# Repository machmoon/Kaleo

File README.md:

# Hardy

**End-to-end PCB design. Describe a board in plain language, get a placed KiCad
layout back — with the reasoning shown and every claim cited.**

**Two names, one thing.** *Hardy* is who you talk to — the AI hardware engineer and
the desktop app in [`app/`](app/). (The spoken wake word is still "Ada", from the
app's previous name.) *Silkscreen* is the engine underneath: the Python package, the
`silkscreen` command, and this repository. Hardy is a client of Silkscreen; either
can be used without the other.

Silkscreen reads the datasheets, proposes a circuit, refuses to build it if it does
not validate, **draws a schematic**, generates the footprints, places the board with a
CP-SAT solver, **routes the copper**, and then argues against its own design and tells
you what it thinks is wrong.

**Silkscreen is a Python program you run.** The command line is the product; the web UI
is a viewer for what it produced, and is the less-supported path — see
[Which interface](#which-interface).

<!-- SCREENSHOTS WANTED — do not uncomment until the files exist under docs/img/:
     docs/img/review.png    the review pane with findings and citations
     docs/img/schematic.png the Schematic tab
-->

---

## Quickstart

Python 3.11 or newer. **No KiCad install or API key is needed to install it or
run the whole test suite. After dependencies are installed, the suite itself
makes no network calls.**

**One command.** It finds a Python 3.11+, creates `.venv`, installs the engine editable
with its extras, and builds the web UI if Node 22+ is on your PATH (skipped, not fatal,
if it isn't). Nothing is written outside the repo and it never uses `sudo`:

```bash
git clone https://github.com/machmoon/silkscreen && cd silkscreen
./scripts/install.sh                                           # macOS / Linux
powershell -ExecutionPolicy Bypass -File scripts\install.ps1   # Windows
```

Then, optionally, one command to configure a key and one to open the app:

```bash
./.venv/bin/silkscreen setup    # writes .env; never echoes the key back
./.venv/bin/silkscreen serve    # starts the API + UI and opens the Hardy desktop app (--web for the browser)
```

<details>
<summary><b>Or install by hand</b> (three lines, same result)</summary>

```bash
python3 -m venv .venv
./.venv/bin/pip install -e ".[dev,agents,cloud,adk,cad]"   # Windows: .venv\Scripts\pip
./.venv/bin/python -m pytest -q                    # offline; no keys required
```
</details>

<details>
<summary><b>Or run the web UI in Docker</b> (no Python or Node on your machine)</summary>

```bash
docker build -t silkscreen .
docker run -p 8080:8080 -e GOOGLE_API_KEY=... silkscreen   # http://localhost:8080
```

The image builds the Svelte bundle in a Node stage and serves it from the Python
service, same origin as the API.
</details>

Then place a board — no API key, nothing to configure, and it finishes in about
20 seconds:

```bash
./.venv/bin/python scripts/demo.py
```

To go from a prompt to a board you need a Gemini key (`GOOGLE_API_KEY`); everything
else works without one:

```bash
./.venv/bin/silkscreen setup    # or: cp .env.example .env, and edit it
./.venv/bin/silkscreen "a 3.3V motor driver around an STM32F103" -o board.kicad_pcb
```

`setup` and `serve` are the only subcommands; any other argument is the plain-language
intent, so `silkscreen "..."` and `python -m silkscreen "..."` are the same generator.

One run leaves you a KiCad project, one file per stage:

```
wrote board.kicad_pro          ← open this in KiCad
wrote board.kicad_sch          ← the schematic
wrote board.placed.kicad_pcb   ← after placement, before any copper
wrote board.kicad_pcb          ← routed
```

Every stage is a real KiCad file you can open and inspect on its own, so you can see
where a design went wrong instead of only seeing the last artifact.

```
3356 tests collected — no network, no API key, no KiCad install
```

**Next:** [full install guide and troubleshooting](docs/install.md) ·
[contributing](CONTRIBUTING.md) · [how it works](#prompt-to-pcb)

**Download:** [tagged releases](https://github.com/machmoon/silkscreen/releases) carry the
Python wheel and built web UI. The native **Hardy** macOS shell currently runs
from a checkout; `.dmg` packaging, signing, and notarization are not yet built.

---

## Which interface

| | `python -m silkscreen` *(recommended)* | Web UI |
|---|---|---|
| Schematic (`.kicad_sch`) | ✅ | ❌ not surfaced |
| Routed copper | ✅ | ✅ in the downloaded file only — the board well draws placement, not tracks |
| Per-stage files you can open | ✅ | ❌ final board only |
| KiCad project (`.kicad_pro`) | ✅ | ❌ |
| Adversarial review, findings, citations | ✅ text | ✅ nicer to read |

**The CLI is still the complete project-output path.** The web UI (`service/` +
`frontend/`) now starts with a persistent orchestrator chat, shows the observable model,
tool, validation, and retry activity, and hands you compact cards for the schematic,
placement diagram, review, and final `.kicad_pcb`. It still does not return the native
`.kicad_sch`/`.kicad_pro` or draw routed tracks, so use the CLI when those files matter.

---

## How you are meant to run this

**Not to run Silkscreen. Yes, strongly recommended, to do anything with what it makes.**

Silkscreen writes the KiCad formats itself, so nothing in the pipeline shells out to
KiCad, imports `pcbnew`, or touches your mouse. But the output *is* a KiCad project,
and without KiCad you have files you cannot open, check, or fabricate. Silkscreen's
router leaves hard nets unrouted on purpose and tells you which — finishing them is
work you do in KiCad. Install it unless you have a specific reason not to.

| | Without KiCad | With KiCad *(strongly recommended)* |
|---|---|---|
| Generate a schematic and a routed board from a prompt | ✅ | ✅ |
| Run the test suite | ✅ | ✅ |
| Deploy the service, use the MCP server or the Slack bot | ✅ | ✅ |
| **See the schematic and the board** | ❌ | ✅ |
| **Finish the nets the router left unrouted** | ❌ | ✅ |
| **Run DRC and electrical rules check** | ❌ | ✅ |
| **Export Gerbers and get it fabricated** | ❌ | ✅ |

Skip KiCad if you are running Silkscreen in CI, on a server, or inside another tool
that consumes the file. Install it if you are a person who wants to see a board.
Platform-by-platform commands are in [docs/install.md](docs/install.md#kicad-optional-but-recommended).

---

## Status

| Component | State |
|---|---|
| `kicad.py` — `.kicad_pcb` read/write | **Working** · 33 tests |
| `packing.py` — CP-SAT placer | **Working** · 44 tests |
| `netlist.py` — validated circuit IR | **Working** · 31 tests |
| `schematic.py` — `.kicad_sch` + `.kicad_pro` emission | **Working** · 38 tests · KiCad ERC clean |
| `routing.py` — two-layer grid autorouter | **Working, partial by design** · 54 tests — see below |
| `footprints.py` + `board.py` — land patterns, board emission | **Working** · 35 tests |
| `agents/` — datasheet, propose, review, pipeline | **Working** · 72 tests |
| `agents/adk/` — ADK dynamic-workflow driver for the pipeline | **Working** · 21 tests |
| `agents/retrieval.py` — page-cited datasheet retrieval | **Working** · 15 tests |
| `agents/resilience.py` — provider failover | **Working** · 31 tests |
| `fab.py` — Gerber, Excellon, BOM, pick-and-place | **Working** · fab package export |
| `order.py` — order options, manufacturability preflight | **Working** · blocks an unrouted board |
| `sourcing.py` + `models3d.py` — BOM with distributor-checked MPNs, probed datasheets, library 3D models | **Working** · an MPN is `verified` only when Mouser lists that exact part number (`MOUSER_API_KEY` required); otherwise `proposed`, with `verify_error` saying why. `verified` means listed, **not** in stock and **not** the right package |
| `mcp/` — MCP server over stdio | **Working** · 43 tests |
| `audit/` — optional visual design review | **Working** · 52 tests |
| `service/` — Cloud Run + Firestore cache | **Working** · 158 tests · deployed once to <https://silkscreen-vqdj4x5qbq-uc.a.run.app>, **currently down** (`/readyz` → 500, `/` → 503 on 2026-09-06, unhealthy since 2026-09-05). Redeploy with `scripts/deploy.sh` and re-verify with `curl -s -o /dev/null -w '%{http_code}' <url>/readyz` before a demo |
| `slackbot/` — Slack bot over the pipeline | **Working** · untested against a live workspace |
| `googleapps/` — Chat, Gmail and Calendar delivery over the pipeline | **Working** · untested against live Google APIs |
| `specreview.py` + the `spec_review` destination — a run's open questions become a booked meeting | **Working** · the Calendar half is untested against live Google APIs |
| `zoombot/` — Zoom front end over RTMS | **Partial by design** · receive and chat halves built, tested offline only; audio out is a spec plus a refusing stub; never run against a live Zoom account |
| `teamsbot/` — Microsoft Teams front end over Graph | **Partial by design** · transcript and chat halves built, tested offline only; the calling bot answers 501; never run against a live tenant |
| `GET /integrations` + the desktop Integrations panel | **Working** · read-only configuration state, never a secret and never a live call |
| `frontend/` — Svelte review UI, served by the service | **Working** · persistent orchestrator chat, expandable traces, session JSON, review, schematic, placement and board tabs; spoken intent and findings read aloud via the browser's own Web Speech API (dictation on the intent and clarification fields in Chrome/Edge — Firefox has no recognition API and gets a notice; findings read by `speechSynthesis` with a stop control; never auto-started). Local-Whisper dictation is not built (`vendor/openwhispr/` is the reference) |
| `engine/silkscreen/placement/` — verifier-grounded repair and company profiles | **Working** · deterministic and Gemini policies; experimental providers are opt-in |
| `constraints.py` — approved build contract and post-route receipt | **Working** · opt-in, fail-closed, and deterministically tested |
| Voice / talk input | **Working** · push-to-talk and "Ada" wake word in the desktop overlay (ear toggle, off by default, paid windows capped at 15); the web SPA's separate browser Web Speech dictation and read-aloud are listed under `frontend/` |
| `app/` — the Hardy desktop overlay (Tauri) | **Working** · approval-gated step strip over a live KiCad, order step with GLB export, in-app 3D board viewer (`ModelViewer`), Workspace delivery panel |
| Guided cursor | **Half built** · the in-webview pointer ships (`frontend/src/lib/guide.js`, `GuidePointer.svelte`, "Show me" on a finding); pointing at anything *outside* our own window — KiCad, a terminal, the OS — is **not built**, and there is no screen capture, accessibility-tree read or OS overlay behind it |
| `spice/` — typed testbenches, decks, measurements, signed-margin assertions | **Working as a library** · reached today only by the MCP tools, `scripts/simulate_demo.py` and direct calls; **no pipeline stage, ADK node, CLI flag or service route builds a deck**, so a generated board is never simulated |

Every module above is covered by tests that run with no network, no API key, and no
KiCad install. The count is deliberately not quoted here — it drifts, and
`scripts/check_docs.py` fails CI when a quoted one goes stale.

---

## PCB placement agent

After the normal placer produces a board, Silkscreen projects its canonical
integer-nanometre geometry into a bounded millimetre verifier, accepts only
score-improving moves, writes accepted positions back to the canonical board,
and only then routes copper. If the company profile needs more edge or clearance
space than CP-SAT's tight outline provides, the adapter minimally expands that
outline before repair. The placement view shows the before and after geometry
together with a receipt for every proposed move.

The legality boundary is deterministic: board bounds, courtyard clearance,
keepouts, and fixed parts. Company preferences are lower-priority terms for
functional grouping, connector access, compactness, and thermal separation.
Gemini may propose `PLACE` and `MOVE` actions, but it cannot override the
verifier. The model-free policy remains available for reproducible runs.

Ollama, Tinker, hybrid policy selection, and training traces are behind an
**Experimental placement features** control that is off by default and enforced
again by the service. Trace recording requires separate explicit consent.
The focused lab keeps corrections in that browser tab's session storage. The
public endpoint applies feedback to one request only; durable shared company
memory remains intentionally unavailable until tenant authentication exists.

The focused `/?mode=placement` lab remains available for comparing the two
included company profiles. See [the placement-agent architecture](docs/placement-agent.md)
for the agent, supervised fine-tuning, reinforcement learning, and verifier boundary.

---

## Approved build constraints

The main prompt form has an optional **Verified constraints** editor. It is collapsed
and disabled by default, so the ordinary prompt-only demo is unchanged. When enabled,
the editor requires exact net names, measurable limits, and an explicit engineer
approval. Any prompt or manifest edit clears that approval. Version 2 manifests are
strict: unknown fields, unknown constraint kinds, duplicate ownership, unsupported
layers, and zero-area physical limits are rejected before cache access or a model call.

The approved manifest is included in the circuit-proposal context, then checked again
against the validated circuit, final placement, and routed copper. The receipt reports
verified, violated, unresolved, and not-required checks for connectivity, routed
geometry, pull-ups, board outline, keepouts, fixed placements, and other declared
limits. Claims that need evidence this engine does not have—such as controlled
impedance without a stackup/field solver, plane continuity, component height, or a
complete voltage-drop model—remain **unresolved** and block production-promotion
eligibility rather than being guessed.

This is currently a post-build eligibility receipt, not a second placer or router.
Board dimensions, keepouts, fixed locations, and soft weights do not yet configure the
CP-SAT or A* solve directly. Soft terms score the one generated result for comparison;
they do not prove that alternatives were ranked. A blocked receipt leaves the generated
KiCad artifact available for inspection, but the orchestrator identifies it as not
eligible for production promotion.

---

## Prompt to PCB

```bash
echo 'GOOGLE_API_KEY=...' >> .env
python -m silkscreen "a 3.3V motor driver board around an STM32F030" \
    --datasheet "AMS1117-3.3=https://.../ams1117.pdf" \
    -o board.kicad_pcb
```

```
intent ─► datasheets ─► propose/validate ─► CP-SAT place ─► verifier repair
                                                                │
               .kicad_pcb ◄─ route ◄─ .kicad_sch + placed board ◄┘
                     │
                     └─► adversarial review
```

| Stage | Module | Artifact |
|---|---|---|
| Datasheet reading (Gemini native PDF vision) | `agents/datasheet.py` | |
| Retrieval over datasheet text, page-cited | `agents/retrieval.py` | |
| Circuit proposal into the IR | `agents/propose.py` | |
| Validation + bounded repair loop | `netlist.py` | |
| Schematic drawing | `schematic.py` | `.kicad_sch`, `.kicad_pro` |
| Footprint generation, board emission | `footprints.py`, `board.py` | |
| Placement | `packing.py` | `.placed.kicad_pcb` |
| Verifier-gated placement repair | `placement/` | placement receipt |
| Copper routing | `routing.py` | `.kicad_pcb` |
| Part sourcing, in the background from placement on | `sourcing.py`, `agents/sourcing.py` | `bom.csv` |
| Approved constraint verification | `constraints.py` | promotion receipt |
| Adversarial review | `agents/review.py` | |

Useful flags: `--no-route` stops after placement, `--no-review` skips the adversarial
pass, `--board-only` writes just the routed `.kicad_pcb`, `--time-limit` sets the
solver budget, `--repairs` how many times a bad proposal goes back to the model,
`--bom` also sources the parts (see [Sourcing the parts](#sourcing-the-parts)), and
`--case` also designs a 3D-printable enclosure — with `--case-style` for a
natural-language case intent ("rounded corners, USB cutout left") and `--rigorous` to run
the case proposal's full strict verify-and-repair loop instead of the demo-fast default,
where a fit failure rides the receipt as a warning rather than blocking the run.

The schematic and the board are drawn by two emitters from one `CircuitSpec`, and both
take their reference designators from `CircuitSpec.assign_refs()` — so `C1` on the
drawing is `C1` on the board. Numbering them separately would give two files that are
each internally consistent and describe different circuits.

Two gates sit between the model and the board.

**Structural.** The proposal goes through the circuit IR before anything is built.
Every validation error is collected and fed back as one repair prompt; the loop is
bounded and `result.repair_rounds` reports how many corrections it took.

**Semantic.** A reviewer re-reads the datasheets and is prompted to *refute* the
design — an agent asked "is this correct?" says yes. Findings are graded
blocker / marginal / note and cite the datasheet page. A part reference the circuit
does not contain is stripped out of the finding that named it; the finding itself
is still shown.

Everything below `agents/` is model-free and network-free, so the whole pipeline —
including its failure paths — is tested against a scripted model with no API key.

### Drawing the schematic

`schematic.py` renders the validated `CircuitSpec` as a KiCad 8 `.kicad_sch`, plus the
`.kicad_pro` that ties the schematic and the board together as one project.

Symbols are **generated, not looked up**. The file carries its own `lib_symbols` block,
the same way `footprints.py` generates land patterns rather than reading a library — so
it opens on a machine with no KiCad symbol libraries installed, and cannot silently
resolve to a different part than the one it was drawn for. Each passive type gets its
own body: a schematic whose crystals are drawn as capacitors reads as correct and
is not.

Connections are a short wire stub from each pin to a **net label**, which is ordinary
KiCad practice and electrically identical to point-to-point wires. The netlist KiCad
extracts from the sheet is the netlist the board was built from, and a pin on no net
gets no stub and no label rather than a wire to nowhere.

### Routing the copper

`routing.py` is a two-layer grid maze router: A* over a uniform lattice with an explicit
via cost, nets routed one at a time, each net grown outward from its first terminal so
later pins join the nearest point of the tree already laid.

**It is not a competitive autorouter, and the output says so.** A uniform grid cannot
reach every pin of a fine-pitch package. The corners a sequential router paints itself
into are escaped by a bounded rip-up-and-retry pass: a net blocked by earlier copper
lifts the nets in its way, routes, and re-routes what it lifted — deterministically,
inside the same search budget, with pads never ripped. A board can still be genuinely
out of channels, so the contract stays honesty rather than completeness — every net it
cannot finish is **named**, with the reason:

```
Routing: 11/13 nets routed, 47 tracks, 6 vias, 214.3 mm of copper
  unrouted SPI1_SCK: no clear path to one of its 3 pads; the channel is blocked
  unrouted VDDA: its 4 pads collapsed onto 1 distinct grid node(s); the routing
                 grid is too coarse for this footprint
```

Unrouted nets stay as ratsnest in KiCad, for you to finish. A net is all-or-nothing:
half a net's tracks laid down would give a board that looks routed everywhere you
happen to look. Defaults are 0.2 mm tracks, 0.2 mm clearance, 0.4/0.2 mm vias, on a
0.25 mm lattice.

Rotated footprints used to be **refused** here, because `board.py` had a recorded bug in
the anchor it wrote for a rotated part and routing to those coordinates would have turned a
latent placement bug into copper landing on bare laminate. That bug is fixed and the
refusal is gone: `placed_half_extents` and `part_anchor` (`board.py:525,540`) are now the
one definition of where a placed part sits, used by both the emitter and the router's pad
geometry, and they swap the courtyard half-extents at 90°. `grep -n rotat
engine/silkscreen/routing.py` returns nothing — the router no longer has a rotation case to
refuse. `build_board` takes `rotatable_refs` (a ref naming nothing on the board is a hard
error, the `edge_refs` convention) and `engine/tests/test_rotated_anchor.py` pins the
reserved box against the written one, which is the check that catches a regression now that
the emitter and the router share a helper and would otherwise agree with each other while
both being wrong.

`--no-route` stops after placement, which is what every run produced before this
existed.

### Simulating the circuit

DRC answers whether a board can be *made*. Nothing answered whether the circuit
*works* — and that gap is why a design loop cannot close itself: it can produce a
plausible schematic and a manufacturable board with no evidence the thing does what it
was asked for. `spice/` is that missing check, shaped like a test runner rather than a
waveform viewer.

**It is not yet wired into the design loop, and this section is a library tour rather than
a description of what a run does.** No pipeline stage, ADK node, CLI flag or service route
builds a deck — `grep -rn spice engine/silkscreen/agents/` returns nothing — so a board
generated by `silkscreen "..."` is never simulated. What can reach it today: the MCP tools
`simulate_circuit` and `spice_capabilities` (usable by an external MCP client; this repo
configures none), `scripts/simulate_demo.py`, and direct Python calls like the one below.
Closing the loop needs a stage body, a workflow node, and a decision about what a failed
clause should do to a run. None of that exists yet; everything described below does.

```python
from silkscreen.spice import Assertion, Measurement, Source, Testbench, Transient, verify

bench = Testbench(
    analysis=Transient(step=1e-6, stop=2e-3),
    sources=[Source.pulse("V1", "VIN", "GND",
                          initial=0, pulsed=5, width=1e-3, period=2e-3)],
)
report = verify(spec, bench, [
    Assertion(name="rise time under 250 us",
              measurement=Measurement(kind="rise_time", signal="VOUT",
                                      window=(0, 1e-3)),
              op="<", value=250e-6, unit="s"),
])
report.passed        # bool
report.summary()     # which clause failed, and by how much
```

`python scripts/simulate_demo.py` runs it end to end against an RC low-pass, checking
every result against closed-form circuit theory:

```
  PASS  10-90% rise time is tau*ln(9)
        measured 0.00021946s, expected within 0.000219503s (margin -4.28e-08)
  PASS  -3 dB corner is 1/(2*pi*R*C)
        measured 1593.23Hz, expected within 1593.14Hz (margin -0.0889)
```

**Nothing here can return a quiet zero.** An agent that gets an empty result reads it as
a circuit that behaves. So a missing model, a probe on a net that does not exist, a
signal with no rising edge, and a solver that will not converge each raise a distinct,
self-describing error. A measurement that cannot be taken fails its clause rather than
passing it vacuously.

**Where it stops, plainly.** A device (an IC) in the circuit IR is a pin map with no
behaviour attached, and no netlist generator can invent one. Trusted Python code can
supply a `SubcircuitModel` — the part's own SPICE model — directly on `Testbench`.
The MCP/JSON tool deliberately does not accept raw SPICE programs; IC simulation there
waits for a trusted server-side model registry. Without a model the run raises and names
the part rather than quietly leaving it out. Passive networks need nothing extra. A
diode with no model gets a generic silicon stand-in and a warning saying so;
`Testbench(strict=True)` turns that warning into an error, which is what you want when
the verdict has to be about the specified part.

ngspice and LTspice sit behind one interface, selected automatically. ngspice is what CI
installs and what this is verified against; LTspice discovery and batch invocation are
implemented but have not been run end to end — see the note in
`spice/simulators.py`. Install ngspice with `brew install ngspice` or
`apt-get install ngspice`; without a simulator the simulation tests skip and the rest of
the suite is unaffected.

---

### Generating footprints

Emitting a board means generating real land patterns: pads at real coordinates, a
courtyard, silkscreen. `footprints.py` builds them parametrically — chip passives
(0402–1210), SOT-23, SOT-223, SOIC, LQFP — so a board can be written with no KiCad
install and no footprint library on disk. Courtyards are fitted to enclose every pad
*and* the body, which is what makes the placer's clearance guarantee mean anything.

Coverage is narrow on purpose and it **raises rather than guessing**. A wrong footprint
is the most common cause of a dead first-spin board; inventing a land pattern for an
unrecognised package would be worse than refusing. Capacitor packages widen with value
(a 22 µF part does not fit an 0603), and output is byte-identical across runs, so a
regenerated board diffs cleanly in git.

### Sourcing the parts

While the engineer is looking at the placed board, the engine looks up the parts.
`--bom` on the command line (and the `sourcing` step in the desktop overlay, which
starts the moment placement lands and needs nothing pressed) asks the model for a
manufacturer, a part number and a datasheet URL per part, given the value and the
land pattern the board actually carries. The result is a `bom.csv` beside the
project, the same rows in the order manifest, and a counts line.

Read the statuses literally, because they are chosen to be. **A part number is a proposal
until a distributor says otherwise.** With no `MOUSER_API_KEY` set there is no verifier at
all and every MPN stays `proposed` — the honest word for a part number nobody checked — and
the model is told that a null beats an invention, because a wrong MPN gets ordered and a
null gets looked up by a person. With a key, `agents/distributor.py` asks Mouser's Search
API v2 for an exact part-number match and the status becomes `verified` only when a
distributor returned a part with that exact `ManufacturerPartNumber`; the row then also
carries `distributor_sku` and `distributor_url`. Everything else keeps `proposed` **and says
why in words** in a `verify_error` field: `Mouser does not list <mpn>` when the search came
back empty, or the failure — a network error, a non-2xx, an unparseable body, an `Errors`
entry (an invalid key answers that way) — when the question could not be answered at all.
The first unanswerable question stops the batch, because a dead API is not asked once per
part, and every row it never reached is marked "not asked" with the same reason rather than
left looking checked; so is every row past the 20-second verification budget. Two things
`verified` still does not mean: **not** that the part is in stock, and **not** that the
package matches the land pattern on the board — Mouser's `Package / Case` field is free text
("SOT-223-4", "SOT-223-3") that cannot be compared to a footprint mechanically, so it is
passed through for a human to read and never used to downgrade a hit. **A datasheet is
`verified` only when
a probe fetched the URL and the first five bytes read `%PDF-`.** Distributors serve
HTML viewer pages from `.pdf` links, and a link that opens a web page is not a
datasheet an engineer can file; that case is reported as `not_pdf`, a URL that could
not be fetched at all as `unreachable`, and a URL the probe budget never reached as
`unprobed` — never as though it had passed. A model answer that fails validation goes back
once as a single batched repair prompt, and after that the BOM comes back unsourced —
every row present, every status `none`, one warning saying why — rather than half
filled in.

Each row also names the **3D model** for its footprint, taken from KiCad's own library
(`${KISYS3DMOD}/…`, the alias every KiCad since 5 resolves to the models it installed)
and written into the `.kicad_pcb`. Nothing is shipped; the board names a model and
KiCad supplies it. A `.kicad_pcb` has no Z, so without these the GLB the order step
exports is a bare substrate — with them, the parts are on it. The table only claims a
model whose body and pin pitch match the land pattern drawn; a package with no honest
match (a 2-pin chip crystal, a narrow-body SOIC-20) gets no model and a reason, not a
picture of a different part.

---

## KiCad integration

Most AI-and-KiCad tools are plugins: they live inside KiCad's Python environment and
drive the IPC API, so they need KiCad running, a supported KiCad version, and a
platform KiCad's plugin loader is happy on. Silkscreen takes the other route — it
treats the board file as the interface.

| | Plugin / IPC approach | Silkscreen |
|---|---|---|
| Requires KiCad installed | Yes | **No** |
| Requires KiCad running | Yes | **No** |
| Headless / CI | Hard | **Native** |
| Platform lock | KiCad's plugin loader | **None — pure Python** |
| Testable without KiCad | No | **Yes, all 3356 tests** |

### What it reads

`load_board()` → `extract_parts()` returns a `FootprintInfo` per footprint:

| Field | Source |
|---|---|
| `width_nm` / `height_nm` | `F.CrtYd` courtyard, falling back to the pad bounding box |
| `pad_offsets` | Per-pad offsets from the part's bottom-left, **flipped into a Y-up frame** |
| `pad_nets` | Net name per pad, used to build the wirelength objective |
| `library_id` | Footprint library nickname |

`extract_nets()` turns shared nets into HPWL nets; `extract_wires()` emits pad-pairs.

### What it writes

- **Footprint positions** — `apply_placements()` moves every footprint, converting the
  solver's Y-up frame back to KiCad's Y-down, anchoring on the courtyard, not the origin.
- **`Edge.Cuts` outline** — `set_board_outline()` draws the board rectangle. Without it
  the file has no boundary at all, and `Edge.Cuts` is both what KiCad measures edge
  clearance against and the only representation of the edge that `must_be_on_edge` was
  solved against.
- Pads, silkscreen, `F.Fab`, courtyards, nets, and zones pass through untouched.

### Units and compatibility

Everything is **integer nanometres**, KiCad's own internal unit, end to end. Unit
confusion between mm, mils, and nm is a silent, board-destroying class of bug, so there
are no floats in the pipeline; the solver quantises to a configurable grid (default
0.05 mm) rather than solving at 1 nm.

| | |
|---|---|
| Board format | `kicad_pcb` version `20240108` (KiCad 7–8) |
| Parser | `kiutils` 1.4.8 — pure Python |
| Solver | OR-Tools CP-SAT 9.15 |
| Python | 3.11+ |
| OS | macOS, Linux, Windows — identical behaviour |

Round-trip is verified by test: a written board reparses, preserves every footprint,
and has no two overlapping courtyards.

---

## Placing a board you already have

Silkscreen can also be used as a library on an existing `.kicad_pcb`, with no
model involved at all — read it, re-place it, write it back:

```python
from silkscreen.kicad import (
    load_board, extract_parts, extract_nets, to_parts,
    apply_placements, set_board_outline, save_board,
)
from silkscreen.packing import pack

board  = load_board("my_board.kicad_pcb")
infos  = extract_parts(board)              # courtyard extents + pad offsets, in nm

result = pack(
    to_parts(infos, edge_refs={"J1"}),     # connector pinned to a board edge
    nets=extract_nets(infos),              # power rails down-weighted, not dropped
    clearance_nm=250_000,                  # 0.25 mm between courtyards
    time_limit_s=20.0,
)

apply_placements(board, infos, result.placements, result.board_height_nm)
set_board_outline(board, result.board_width_nm, result.board_height_nm)
save_board(board, "placed.kicad_pcb")
```

Reproduce it with `python scripts/demo.py`, on the 11-footprint STM32 + regulator +
motor-driver fixture in `engine/tests/fixtures/`:

```
11 footprints, 6 nets
status     : feasible
board size : 18.25 x 18.00 mm  (328.5 mm²)
HPWL       : 53.0 mm
placed 11/11 -> placed.kicad_pcb  (~43.9 kB, reparses clean)
```

**Read that block for what is reproducible and what is not.** Stable on every run: 11
footprints, 6 nets, `status: feasible`, 11/11 placed, and a written file that reparses with
every footprint and no overlapping courtyard — the round-trip property the tests enforce.
**Not stable: the board size and the HPWL.** `scripts/demo.py` passes `time_limit_s`
(default 20 s) and the solve ends "time limit reached; feasible but not proven optimal", so
the answer is whatever the search had reached when the clock ran out — and that depends on
how much CPU the machine gave it. Measured on one Mac on 2026-09-06: six idle runs all gave
`18.25 x 18.00 mm` / `53.0 mm`; six runs launched concurrently all gave
`19.60 x 18.55 mm` / `62.0 mm`. Same code, same seed, same `workers=1`. So the figures above
reproduce on a quiet machine and should not be treated as a benchmark or quoted as a
constant; if yours differ, that is the time limit, not a regression. `workers=1` (the
default) is still required for even that much — CP-SAT's multi-worker portfolio interleaves
results non-deterministically regardless of seed — and raising `--time-limit` until the
status reads `optimal` is what makes the number genuinely machine-independent.
(That run omits `edge_refs`: the fixture has no connector, and naming a ref that isn't on the
board is an error, not a no-op.)

One caveat, since this is the only measured figure here: the fixture's nets are named
`0_device_pin_N` by the pipeline that generated it, so none match the power-rail heuristic
and the power-net weighting described below **does not fire on this board**. It is exercised
by unit tests, not by the number above.

---

## Running it other ways

### As a service

```bash
gcloud run deploy silkscreen --source . --region us-central1 \
  --set-secrets GOOGLE_API_KEY=google-api-key:latest \
  --set-env-vars GOOGLE_CLOUD_PROJECT=your-project
```

A live instance is running at
<https://silkscreen-vqdj4x5qbq-uc.a.run.app> (deployed 2026-08-31, project
`project-e9121780-d00d-4f9b-8b5`; the Gemini key comes from Secret Manager and
`POST /generate` requires an access token, so browsing to it costs nobody
anything). Probe liveness with `GET /` or `/readyz`, not `/healthz` — Google's frontend
intercepts `/healthz` on `run.app` domains at the edge and answers 404 before
the request reaches the container. Verify before a demo:
`curl -s -o /dev/null -w '%{http_code}' https://silkscreen-vqdj4x5qbq-uc.a.run.app/readyz`
should print `200`. **It does not today.** Checked 2026-09-06: `/readyz` answered `500`,
`/` answered `503`, and `/healthz` answered the edge's `404` — the same outage first seen on
2026-09-05, now at least two days old. Treat the URL as **down until re-verified**: redeploy
with `scripts/deploy.sh`, then `scripts/smoke.sh --health-only <url>`, before quoting it
anywhere or showing it to anyone. A recorded deploy is not a running one.

`POST /generate` with `{"intent": "...", "datasheets": {"PART": "url"}}` returns
the board, the emitted `.kicad_pcb`, and a versioned `schematic` topology block
with stable part ids, board refs, pins and structured net endpoints. Extracted
datasheet facts persist to Firestore, so the second request for a part skips the most expensive stage.
`POST /chat/stream` is the presentation path: a genuine ADK `LlmAgent` may ask one
essential clarification and otherwise calls the validated generator as its
`generate_board` tool. It streams versioned NDJSON events for the orchestrator, tool,
worker calls, and final result. `GET /models` discovers the current key's
`generateContent`-capable Gemini models, with a short server cache and configured fallback
catalog. `GET /healthz` and `GET /readyz` both answer the readiness JSON in-container — but
probe the deployed instance with `/readyz` or `/`, never `/healthz`, for the edge reason
given above. The container serves the built UI at `/`,
same origin as all of these routes, so there is no CORS anywhere.

`GET /config/status` backs the live backend-readiness section in the right side rail.
It reports whether Gemini, ADK, Ollama, Tinker, and Firestore can use the active
process configuration, probes a configured Ollama server for its selected model,
and notices local `.env` edits that require a backend restart. The response contains
variable names and status messages only; it never returns configuration values or
credentials. These checks do not make paid generation calls.

### In Slack

`slackbot/` puts the pipeline in a hardware team's channel. Mention the bot with
what you want built and it replies **in a thread under your message** — a live
stage list, the review, a rendered preview of the placement, and the emitted
`.kicad_pcb` — so the whole team can read the run later, not just whoever asked.

```
@silkscreen design a 3.3V buck converter from 12V --datasheet TPS62840=https://…
@silkscreen place an stm32f103 breakout      # skip the review: faster and cheaper
@silkscreen review                           # re-run the critic on this thread's run
@silkscreen order 25                         # prepare a fab order (never submits one)
@silkscreen help
```

`order` **prepares** a fabrication order and stops: board size, stackup, the files
the run produced, any blocking findings from the review, and what a fabricator still
needs. It posts that draft as a message and a JSON attachment. It does not contact a
vendor, submit anything, or touch a payment method — none of that exists in this
codebase, and a test enforces it by import. A human places the order.

**Running it:**

```bash
./.venv/bin/pip install -e ".[dev,agents,slack]"
export SLACK_BOT_TOKEN=xoxb-… SLACK_SIGNING_SECRET=… GOOGLE_API_KEY=…
python -m slackbot                      # POST /slack/events on :3000
```

Slack has to reach that port, so in development put a tunnel in front of it
(`ngrok http 3000` or equivalent) and give Slack the public URL.

**Creating the app** (once, in your workspace, at <https://api.slack.com/apps>):

1. **Create New App → From scratch**, pick your workspace.
2. **OAuth & Permissions → Bot Token Scopes**: `app_mentions:read`, `chat:write`,
   `files:write`, `reactions:write`. Add `commands` if you want the slash command.
3. **Install to Workspace**, then copy the **Bot User OAuth Token** (`xoxb-…`) into
   `SLACK_BOT_TOKEN`.
4. **Basic Information → Signing Secret** goes into `SLACK_SIGNING_SECRET`. Every
   request is HMAC-verified against it before it is parsed, and requests older than
   five minutes are refused, so a captured one cannot be replayed.
5. **Event Subscriptions → Enable**, request URL `https://your-host/slack/events`.
   Slack verifies the URL with a challenge the bot answers automatically. Under
   **Subscribe to bot events** add `app_mention`.
6. Optionally **Slash Commands → Create**: `/silkscreen`, request URL
   `https://your-host/slack/commands`.
7. Invite the bot to the channel: `/invite @silkscreen`.

Set `SILKSCREEN_SLACK_CHANNELS` to a comma-separated list of channel IDs to confine
runs to the channels that are paying for them; leave it unset to allow any channel
the bot is in. `SILKSCREEN_SLACK_MAX_RUNS` (default 2) caps concurrent runs — a
design run costs model calls and a CP-SAT solve, so six people asking at once should
not start six.

Runs are remembered per thread **in memory**, so `review` and `order` work on the
run above them and a restart forgets them; the bot says so rather than acting on the
wrong board. Artifacts are also written under `SILKSCREEN_SLACK_WORKDIR`
(default `slack-runs/`).

### In Google Workspace

`googleapps/` delivers a finished run to the places a hardware team already
looks: a **Google Chat** space gets a run card, **Gmail** gets the summary with
the emitted `.kicad_pcb` attached, and — only when the adversarial review found
blockers — **Calendar** gets a design-review event with a Meet link:

```bash
python -m googleapps auth        # one command, one browser click-through
python -m googleapps check      # what is configured, is the token valid — no network
python -m googleapps run "a 3.3V LDO board" -o out/board.kicad_pcb \
    --chat \
    --email lead@example.com \
    --schedule --attendee lead@example.com
```

`--schedule` creates the event **only** when the review produced blockers, and
says which way that went either way — a clean review schedules nothing; when
it does schedule, every attendee is actually invited. The pipeline flags are
the CLI's (`-d PART=URL`, `--model`, `--repairs`, `--no-route`, …), and
everything that can be checked before the paid run — key, webhook, addresses,
a usable token — is checked before it. The
card and the email follow the same honesty rule as every other surface here:
every net the router left unrouted is named, verbatim, with the router's
reason; nothing ever says "board ready" over a ratsnest.

Auth is a stdlib OAuth 2.0 installed-app flow with PKCE — no Google client
libraries. The token lands at `~/.config/silkscreen/google-token.json` with
mode 0600 and refreshes transparently; the Chat webhook URL is itself the
credential and is validated (https, `chat.googleapis.com`, a `/v1/spaces/…`
path) before anything is sent to it. Nothing in the package will address a
non-Google host.

Setup — Cloud project, enabling the Gmail and Calendar APIs, creating the
Desktop-app OAuth client and the Chat webhook — is walked through in
[docs/googleapps.md](docs/googleapps.md). **It has not been run against live
Google APIs yet**; the offline tests cover request construction against a
recorded transport, and the first live run should be treated as the real test.

#### Booking a spec review instead of printing a wall of text

`--spec-review` (and, from the overlay, the Send panel's **Book a spec review**)
turns what a run could not settle into a short agenda and books it:

```bash
python -m googleapps run "a 3.3V LDO board" --spec-review --attendee lead@example.com
```

The agenda is validated model output with bounds that *are* the feature — a
400-character summary, one to eight items, fifteen to sixty minutes in total —
so it cannot quietly grow back into the report it replaces. An item naming a
part or net the board does not contain is dropped and the drop is reported, the
same hallucination filter the reviewer's findings go through. When nothing
produced an agenda, a deterministic one is built from the blockers and the
ratsnest with no model call at all.

Two things are refusals rather than errors, and the run says which: **the
review step has not run**, so what the meeting would decide is not known; or
**nothing is blocking**, so nothing needs a meeting. Neither books an empty half
hour. The event description names every unrouted net verbatim and is
HTML-escaped, and `sendUpdates=all` means the attendees are actually told.
Run options carry a **Structured / Prose** toggle that chooses whether a
finished run reports itself as this agenda or as prose. Full contract, request
and response JSON, and every refusal:
[docs/spec-review.md](docs/spec-review.md).

### Running the web UI

> Secondary and not well supported — see [How you are meant to run this](#how-you-are-meant-to-run-this).

The UI is a Svelte SPA in `frontend/`, and it needs Node 22 or newer
(`node --version`). In development it runs on Vite's dev server, which proxies
`/generate`, `/chat`, `/models`, `/config`, and `/healthz` to the Python service — two terminals:

```bash
PORT=8081 python -m service.app            # terminal 1: the API
cd frontend && npm install && npm run dev  # terminal 2: http://localhost:5173
```

For the production path, build the bundle and let the service serve it itself:

```bash
cd frontend && npm run build  # writes frontend/dist/
python -m service.app         # http://localhost:8080 serves the UI and the API
```

The UI has its own Vitest suite, which CI runs before the build:

```bash
cd frontend && npm test
```

A run stays in the **Chat** tab as a persistent transcript. Friendly activity summaries
are shown by default; raw orchestrator and worker prompts/responses are expandable for a
demo or debugging. Before submitting, the orchestrator panel selects Gemini 3.7 Flash or
Gemini 3.1 Pro Preview and an Auto/Fast/Standard/Deep thinking effort. 3.1 Pro sits below
the hackathon's Gemini 3.5 floor, so the service refuses it (HTTP 400) unless it runs with
`SILKSCREEN_ALLOW_LEGACY_MODELS=1`; Auto and 3.7 Flash are never gated. Gemini 3 cannot
disable thinking completely, so Fast maps to the supported `low` level. A separate
request-pace control can space every explicit orchestrator and worker attempt at 15, 6,
or 3 RPM across one service instance; Auto preserves the provider default. This mitigates
RPM bursts but cannot raise Google's per-project token or daily quotas. Clarification,
retry, edit, copy-error, and discovered-model retry
controls remain beside the failed or incomplete turn. **Save session** exports a versioned
JSON snapshot containing the transcript, trace, result, and board artifact; **Open session**
restores it locally. Treat that debug export as sensitive if a prompt contains private
design information.

Appearance stays local to the browser. **Glass** in the title bar switches the whole
rendered interface from the opaque Drafting Table skin to a translucent material, while
**Night** independently selects its light or dark reading. Both choices persist across
reloads; reduced-transparency system settings replace blur with opaque surfaces, and the
PCB canvas keeps its fixed KiCad colours in every combination.

The compact artifact cards open the existing views. **Schematic** draws the validated
circuit as generic symbols with physical pin numbers and net-labelled connections; it does
not claim to be a native `.kicad_sch` or a library-accurate sheet. **Board** draws the
placement the service actually produced — courtyard outlines, pads, and part refs — while
**Review** shows the grounded findings. Selecting a finding highlights the parts it names,
and the board and review panes offer the emitted `.kicad_pcb` as a download.

`silkscreen serve` does both of those for you — it loads `.env`, starts the service on
`--port` (or `PORT`), and opens the browser. Running `python -m service.app` directly
does **not** read `.env`; only the CLIs do, so export the key first. See
[docs/install.md](docs/install.md#the-env-caveat).

### As an MCP server

```bash
silkscreen-mcp        # JSON-RPC 2.0 over stdio
```

Tools: `validate_circuit`, `build_board`, `emit_kicad_pcb`, `place_parts`,
`generate_footprint`, `simulate_circuit`, `spice_capabilities`.

`simulate_circuit` accepts typed sources (`dc`, `ac`, `pulse`, `sine`) and typed
analyses only. Unknown fields and raw model/directive text are rejected before a
simulator starts; runtime is capped at 120 seconds and returned waveforms at 2,000
points per signal. `spice_capabilities` reports simulator names without exposing local
executable paths.

### In Google Meet

`meetings/` reads the transcript of a meeting that already happened and drafts a
board for what the meeting asked for. **Read the limits before the feature:**

- It reads a conference **after it ends**, not while it runs. Nothing listens
  live; a live listener would need the Meet Media API, which is a different and
  much larger piece of work.
- It only sees a meeting where the **organiser turned transcription on**. No
  transcript means no input, and the run says so rather than reporting an empty
  meeting.
- It does **not** join the call. There is no headless browser, no fake
  participant, and no media plumbing — every open-source meeting bot works that
  way, and this deliberately does not. It is the Google Meet REST API v2 and
  nothing else.
- It has **never been run against a live Google Workspace account**. The Meet
  API path is unverified live: every test drives a recorded transport offline.

Configuration is environment only, and the package does **not** perform the
OAuth flow — the host supplies an already-obtained bearer token:

```bash
export MEET_ACCESS_TOKEN=...   # required; scope meetings.space.readonly
export MEET_SPACES=spaces/abc,spaces/def  # optional allowlist; empty = every conference the token can see
export MEET_API_BASE=https://meet.googleapis.com/v2  # optional, pinned by default
export MEET_MAX_AGE_HOURS=24   # ignore conferences that ended longer ago
export MEET_MAX_RUNS_PER_POLL=3  # cap the board runs one poll may start
```

Token acquisition, refresh and storage belong to the host application. The scope
is read-only on purpose: nothing here creates, modifies or joins a meeting.

What survives the meeting is **drafted, not ordered**. A request whose quote is
not in the transcript is dropped, a request below the confidence floor is
recorded but not built, and every skipped request is still reported — a bot that
quietly ignores what someone asked for is the failure people actually hit.
Nothing is ever purchased.

The board itself comes from the same generator the CLI uses, so this is a
different way to supply the sentence, not a second pipeline. When the output
files matter, `python -m silkscreen "..."` remains the complete path.

### In Zoom

`zoombot/` goes one step further than `meetings/` and works *while* the call is
happening: it ingests the meeting's live transcript over Zoom's Realtime Media
Streams, extracts board requests from what was actually said, runs the
pipeline, and answers in the room.

```bash
pip install -e ".[dev,agents,zoom]"
export ZOOM_CLIENT_ID=… ZOOM_CLIENT_SECRET=… ZOOM_ACCOUNT_ID=… \
       ZOOM_WEBHOOK_SECRET_TOKEN=… GOOGLE_API_KEY=…
python -m zoombot       # POST /zoom/events, GET /healthz, on ZOOM_PORT (default 8095)
```

**Read the limits before the feature:**

- It has **never been run against a live Zoom account**. Every network boundary
  is a Protocol seam with a recorded stand-in, so the suite proves the parsing,
  the gates and the refusals — and nothing about Zoom's live behaviour.
- **RTMS is receive-only.** Nothing in that API puts audio back into a meeting.
  Speaking out loud needs a real participant, which is the headless Meeting SDK
  container in `zoombot/bot/` — **not built and not run by the test suite**,
  with a control stub that refuses every `/say` rather than claiming a line was
  spoken. The Zoom SDK binary is downloaded under Zoom's licence and is not
  vendored here.
- The RTMS **frame constants are assumptions from Zoom's own sample, not
  measurements**, gathered in one block so a first live run can correct them in
  one place. [docs/zoom.md](docs/zoom.md) lists every one.
- `ZOOM_SPEAK_MODE` picks `sdk` (audible), `chat` (a message in the meeting
  chat) or `off`, and every report names which speaker was used — "the agent
  replied" can never be read as "the agent spoke out loud".

The gates are the ones `meetings/` established: a request whose quote is not in the transcript is
dropped, one below the confidence floor is recorded but not built, every
skipped request is still reported, `ZOOM_MEETINGS` bounds which meetings count
and `ZOOM_MAX_RUNS_PER_MEETING` bounds the paid runs. Nothing is ever ordered.
Full setup, scopes and env vars: [docs/zoom.md](docs/zoom.md).

### In Microsoft Teams

`teamsbot/` is the same idea against Microsoft's stack: a Bot Framework
activity in a meeting chat, a Graph calling notification, or a finished
meeting's `callTranscript` read through Microsoft Graph.

```bash
pip install -e ".[dev,agents,teams]"
export TEAMS_APP_ID=… TEAMS_APP_SECRET=… TEAMS_TENANT_ID=… GOOGLE_API_KEY=…
python -m teamsbot      # POST /api/calls, POST /api/messages, GET /healthz, on :3978
```

**The limits, again first:**

- It has **never been run against a live Microsoft 365 tenant**. The offline
  tests drive a recorded Graph transport and validate the inbound JWT against a
  locally generated key pair.
- **Audio out is unbuilt.** A Teams calling bot needs Microsoft's .NET Graph
  Communications media libraries, which are not vendored here; `teamsbot/bot/`
  is the control plane only and its `POST /say` answers **501 Not Implemented**
  with a sentence naming what is missing, which surfaces in the run report.
- The inbound token is verified — algorithm, issuer, audience, validity window,
  signature — **before the body is parsed**, and a missing `cryptography` or a
  missing key source is a *refusal*, never an exemption. That is why
  `cryptography` is in the `teams` extra rather than an optional import.
- A transcript exists only when the organiser enabled transcription, and only
  after Teams has processed it. "Never enabled", "none yet", "not authorised"
  and "the call failed" are four different exception types, because an agent
  handed an empty string concludes the meeting was silent.
- A **Teams application access policy** (PowerShell) is a real prerequisite:
  without it Graph answers 403 for a meeting the app registration otherwise has
  permission for.

Full setup, permissions and env vars: [docs/teams.md](docs/teams.md).

### The Integrations panel

`GET /integrations` answers with every front end and optional tool in one
read-only view — Workspace delivery, Slack, Meet, Zoom, Teams, the enclosure
kernel, sourcing, the MCP server, SPICE and `kicad-cli` — and the desktop app
renders it at `/integrations`, grouped into Delivery, Meetings, Design and
Fabrication.

Four states, and the distinction is the point: `unavailable` (the code is not
here — an optional extra missing, a binary not on `PATH`, a feature not built),
`unconfigured` (importable, nothing set), `partial` (some required settings
present) and `ready`. **`ready` is a claim about configuration and nothing
else** — no route here makes a live call, so nothing in the response may read
as "a round trip succeeded". No secret is ever echoed, not even a tail (a
webhook URL's tail is the token): a credential shows only the
`<set, N chars>` mask. Nothing raises out of it either — a probe that blows up
becomes that one integration's state and hints, never a 500 that hides the nine
that were fine. An integration that is not built yet still appears, marked
`unavailable`, because unbuilt work stays visibly unbuilt.

---

## Reviewing a board

Optional, and separate from generating one. `silkscreen-review` reviews any
`.kicad_pcb` — one this project emitted, or one you laid out yourself — and
marks what it finds **on the board**, not just in a list.

```bash
silkscreen-review board.kicad_pcb                       # standard effort
silkscreen-review board.kicad_pcb -e deep -o review/    # deeper, write reports
silkscreen-review board.kicad_pcb -e quick --no-model   # offline, no API key
silkscreen-review board.kicad_pcb --fail-on-blocker     # exit 1 for CI
```

`-o` writes three files: `review.html` (board render beside the findings,
click either to highlight the other), `review.svg` (the annotated board on its
own, for a PR comment or a slide) and `review.json`.

### The thinking slider

```
quick     ●───○───○   geometry and connectivity. No model call at all.
standard  ○───●───○   + clearance sweeps, decoupling distance, track widths,
                      and one model pass.
deep      ○───○───●   + manufacturing rules, tighter thresholds, a per-part
                      model pass for every IC, and every model finding must
                      survive a refutation prompt before it is reported.
```

Each level runs a strict superset of the level below it — enforced by test, so
"deeper" cannot quietly become "different". Higher levels are slower and, above
`quick`, cost model calls.

### Proven and suggested

The report keeps two kinds of finding apart, because they are not equally
trustworthy:

- **Proven** — measured by a deterministic checker in `audit/rules.py`, and
  shown with the measurement that proves it (`gap 0.100 mm, clearance
  0.300 mm`). Outlined solid on the render.
- **Suggested** — argued by the model: wrong capacitor value, floating mode
  pin, a topology mistake. No measurement, dashed on the render, and dropped
  entirely if it names no part the board contains.

Nothing the model returns can delete, downgrade or reword a proven finding,
and a model failure loses only the suggested half — the report then says why
the model did not run rather than showing a shorter list.

The report also states what was *checked*, so an empty finding list cannot be
mistaken for a clean board when it only means a rule never ran.

---

## The placer

CP-SAT. Variables are each part's bottom-left corner on an integer grid;
`AddNoOverlap2D` enforces disjointness, `AddMaxEquality` derives the bounding box,
`AddAbsEquality` linearises wirelength. The objective minimises board half-perimeter
plus total HPWL.

| Feature | Why it's there |
|---|---|
| **Real clearance** | Parts inflate by `clearance_nm/2` per side before no-overlap. Flush-packed boards can't be assembled. |
| **90° rotation** | A boolean per part swaps interval sizes; pin offsets rotate with two implications, not a centre approximation. |
| **Edge constraints** | Connectors and antennas pin to an edge via a disjunction over four half-reified literals. |
| **Symmetry breaking** | 24 identical caps admit 24! relabelings. Forcing a lexicographic order collapses each orbit to one representative — on a 27-part board, optimality in 0.72 s instead of 16.7 s. |
| **HPWL, one box per net** | A pairwise clique makes a 50-pad ground net contribute 1,225 terms that swamp every signal. A star overestimates length and makes layout depend on footprint order in the file. |
| **Power rails down-weighted, not dropped** | A decap's only connections are VCC and GND — drop power nets and it has no objective term and drifts. Measured: excluding power put a cap 9.65 mm from its IC pin; weighting at 0.25 brings it to 5.15 mm. |
| **Pinned parts** | `Part(fixed_at_nm=(x, y))` holds a part where you put it. Without this every re-solve reshuffles the board, so you can't keep a placement you like and let the solver work around it. |
| **Keepouts** | `Keepout(x, y, w, h)` reserves a region — mounting holes, a connector's mating envelope, a mechanical boss. Modelled as an immovable participant in the same no-overlap constraint as the parts, because that's what it is. |
| **Degrades, doesn't fail** | If CP-SAT finds nothing in budget, a deterministic shelf packer returns a valid layout flagged `FALLBACK`, warning about every constraint it couldn't honour — including the pins and keepouts it can't. |

### Iterating on a placement

Keep what you like and re-solve the rest:

```python
from silkscreen import Keepout, Part

first = pack(parts, nets=nets)
good  = {p.ref: p for p in first.placements}

parts = [
    Part(..., ref="J1", fixed_at_nm=(good["J1"].x_nm, good["J1"].y_nm))
    if p.ref == "J1" else p
    for p in parts
]
second = pack(
    parts,
    nets=nets,
    keepouts=[Keepout(mm(3), mm(3), mm(3.2), mm(3.2), name="MH1")],  # M3 hole
)
```

`fixed_at_nm` names where the **part** goes, not its clearance-inflated box, and is
snapped to the solver grid. Pinning closer to the origin than `clearance_nm/2` raises,
because the clearance ring has to exist.

### Limits

2D packing with a wirelength objective is NP-hard. On real boards the solver returns
`FEASIBLE`, not `OPTIMAL`, inside 20 s — and Silkscreen reports it as `FEASIBLE`.
Coarsening the grid from 0.025 mm to 0.5 mm barely moves the result, so the bottleneck
is combinatorial, not resolution. **Treat the output as a strong starting placement,
not a proof.**

No support for: **two-sided placement** (everything is one layer), **connector
orientation** (`must_be_on_edge` puts a part on an edge but says nothing about which
way it faces), **thermal relief**, or **differential pairs**. Two-sided placement is
the one that most limits real use.

---

## The circuit IR

`silkscreen.netlist` is the contract between a model and anything that touches KiCad.
A model proposes a `CircuitSpec`; nothing is instantiated until it validates, and *all*
failures are collected so the batch goes back as one repair prompt.

Rejects: a pin the device doesn't have · a part that doesn't exist · a bare part name
where a terminal is required (`C1` not `C1.1`) · a passive wired on one leg · a net with
fewer than two endpoints · unsupported passive types.

That fourth check matters most. Connecting *one specific leg* of a decoupling capacitor
to a specific pin is the most common operation in this domain, and an IR that can only
join whole parts to nets cannot express it at all.

---

## Layout

```
engine/
  silkscreen/
    units.py      nm/mm/mil conversion, grid quantisation
    packing.py    CP-SAT placer
    netlist.py    validated circuit IR
    footprints.py parametric IPC-7351 land patterns
    board.py      emit a .kicad_pcb from a circuit
    schematic.py  emit a .kicad_sch and the .kicad_pro that ties them
    routing.py    two-layer A* copper router
    kicad.py      read/modify an existing .kicad_pcb via kiutils
    ids.py        stable UUIDs, so two runs diff cleanly
    cli.py        python -m silkscreen "..."
    spice/        typed testbenches, deck building, simulators, measurements
    placement/    verifier-gated repair + opt-in Ollama/Tinker policy adapters
    constraints.py approved manifest parsing + deterministic post-route receipt
    mcp/          JSON-RPC tools, including the bounded simulation verifier
    agents/       Gemini-backed worker and orchestrator calls
      model.py      provider seam + scripted stand-in for tests
      datasheet.py  PDF -> structured facts, with page citations
      propose.py    intent -> circuit, with a bounded repair loop
      review.py     adversarial design review
      stages.py     shared stage bodies for both drivers
      pipeline.py   prompt -> PCB
      adk/          ADK dynamic workflow over the same stage bodies
    audit/        optional visual review of a finished board
    specreview.py validated meeting agenda for what a run could not settle
  tests/          3356 tests — no network, no API keys, no KiCad
    fixtures/     ref.kicad_pcb -- 11-footprint board fixture
scripts/
  demo.py         end-to-end: read -> place -> write -> verify
  simulate_demo.py closed-form RC checks through a real ngspice run
  check_docs.py   fails CI if a quoted test count goes stale
zoombot/
  rtms.py         webhook verification + RTMS transcript ingest (receive-only)
  speak.py        sdk | chat | off, and which one was actually used
  bot/            headless Meeting SDK participant — spec + refusing stub, not built
teamsbot/
  graph.py        Microsoft Graph: app token, meetings, transcripts (read-only)
  app.py          /api/calls + /api/messages, inbound JWT verified before parsing
  bot/            calling-bot control plane — POST /say answers 501, media half unbuilt
frontend/
  src/
    lib/          api client, run store, severity + format helpers
    components/   title bar, intent form, progress, findings, side rail
    styles/       paper/glass material and light/dark design tokens
  dist/           built bundle -- service/app.py serves it at /
vendor/
  mudriknow/      third-party (MIT), reference only -- not imported, not tested
```

Top-level `mcp/`, `pcb/`, `packing/`, `footprint/`, `frontend-archive/`, `lcsc.py` and
`test_skidl.py` are pre-rewrite hackathon code, not part of the layout above. Their removal
is in progress and **not yet committed** — they are still in `origin/main`, and `git status`
on a checkout that has them deleted shows the deletions unstaged — so run `git ls-files` if
you need to know which state you are in. Either way they are name-collision traps: the live
MCP server is `engine/silkscreen/mcp/`, the live placer `engine/silkscreen/packing.py`, the
live land patterns `engine/silkscreen/footprints.py`. See
[CONTRIBUTING.md](CONTRIBUTING.md).

`desktop/` is **not** uniformly retired. `desktop/kicad_live.py` is live: `service/steps.py`
spawns it by path to show a stage in a running KiCad. `desktop/launcher.py`,
`desktop/sidecar.py`, `desktop/src-tauri/` and `desktop/silkscreen-app` are the pre-Hardy
shell, reached by nothing in the product path; the live desktop app is top-level `app/`.

---

## Troubleshooting

Install and environment problems are in [docs/install.md](docs/install.md#troubleshooting).
Problems with a run:

| Symptom | Cause |
|---|---|
| `edge_refs names refs not on this board` | A ref in `edge_refs`/`rotatable_refs` matches no footprint. The error lists valid refs — a typo would otherwise become a silently missing constraint. |
| `status` is `FALLBACK` | CP-SAT found nothing in budget. Raise `time_limit_s`, coarsen `grid_nm`, or relax `max_board_nm`. Check `result.warnings`. |
| `status` is `FEASIBLE`, not `OPTIMAL` | Expected on real boards. The solution is valid but unproven. |
| Results differ between runs | You set `workers > 1`. Use `workers=1` for determinism. |
| KiCad won't open the output | Confirm the board is format `20240108` (KiCad 7–8). Older KiCad won't read it. |
| Parts overlap in KiCad's DRC | DRC measures pad/copper clearance; `clearance_nm` is *courtyard* clearance. Raise it. |

---

## Reproducible testing

Every result in this README can be reproduced from a clean clone in about four
minutes. **No KiCad install, no network access, and no API keys are required** —
the test suite and the demo both run fully offline.

### Requirements

| | |
|---|---|
| Python | 3.11 or newer (`python3 -V`) |
| OS | macOS, Linux, or Windows — all three run in CI |
| Network | Not needed after `pip install` |
| API keys | None. `agents/` tests use a scripted stand-in model, not a live provider |
| KiCad | Not needed. Board files are parsed by `kiutils`, which is pure Python |
| Disk | ~400 MB, almost all of it OR-Tools |

### From a clean clone

```bash
git clone https://github.com/machmoon/silkscreen.git
cd silkscreen
python3 -m venv .venv
./.venv/bin/pip install -e ".[dev,agents,cloud,adk,cad]"
```

Then run the four Python checks below. The first two are what CI runs (`ci.yml:40-44`);
checks 3 and 4 are local additions CI also runs, in this order:

```bash
./.venv/bin/python -m pytest -q                            # 1. tests     (~30 min)
./.venv/bin/python -m ruff check \
    engine service scripts desktop googleapps zoombot teamsbot   # 2. lint  (~2 s)
./.venv/bin/python scripts/check_docs.py                   # 3. doc drift (~5 s)
./.venv/bin/python scripts/demo.py                         # 4. end-to-end(~20 s)
```

Check 3 re-counts the suite and fails if any number quoted in this README or in
`DEVPOST.md` has gone stale, so those figures cannot drift from the code.

On Windows, use `.venv\Scripts\python.exe` in place of `./.venv/bin/python`.

CI runs two more jobs that need Node 22 and Docker rather than Python, so they
are not in the list above:

```bash
cd frontend && npm ci && npm test && npm run build   # the `web` job
docker build .                                      # the `docker` job
```

### Expected output

**1. Test suite** — live-model and local-simulator cases skip when their
optional dependency is unavailable. Pytest prints the current collected,
passed, and skipped counts; the documentation check below verifies every
quoted test-count claim against that same collection.

The suite is dominated by the 20-second solver budget in a handful of placement
tests; the rest run in milliseconds. Google ADK currently emits one warning for
its experimental JSON-schema function-declaration feature.

**2. Lint:**

```
All checks passed!
```

**3. Doc drift** — re-counts the suite and checks every figure quoted in the docs:

```
docs ok: every test-count claim matches the collected suite
```

**4. End-to-end demo** — reads the 11-footprint fixture board, places it, writes a
real `.kicad_pcb`, and re-parses it to prove the round-trip:

```
3. Solve (OR-Tools CP-SAT)
--------------------------------------------------------------
  status     : feasible
  board size : 18.25 x 18.00 mm  (328.5 mm^2)
  HPWL       : 53.0 mm
  solve time : 20.00 s
  warning    : Time limit reached; solution is feasible but not proven
               optimal (gap bound 696000 vs 1785000).

4. Write a real .kicad_pcb
--------------------------------------------------------------
  placed 11/11 -> placed.kicad_pcb  (43,936 bytes)

5. Prove the round-trip
--------------------------------------------------------------
  reparsed OK, 11 footprints preserved
```

These are the exact figures quoted in [The placer](#the-placer). To inspect the
result, open `placed.kicad_pcb` in KiCad's PCB Editor — but note that installing
KiCad is only ever needed to *look* at the output, never to produce it.

### On determinism

Placement is reproducible **only with `workers=1`**, which is the default. CP-SAT's
multi-worker portfolio search interleaves results non-deterministically regardless
of `seed`, so raising `workers` trades byte-identical output for speed. The
determinism test in `test_packing.py` asserts this contract by solving the same
model twice and comparing placements exactly.

Two caveats worth stating plainly:

- **`status: feasible` is expected, not a failure.** 2D packing with a wirelength
  objective is NP-hard; inside a 20-second budget the solver returns a valid
  solution plus a bound rather than a proof. The reported gap is genuine.
- **The *result* varies with your machine too**, and the earlier claim that only the
  solve time did was wrong. Because the run ends at the time limit rather than at a proof,
  a loaded machine returns a worse feasible solution: six concurrent runs of
  `scripts/demo.py` on the same Mac that gives `18.25 x 18.00 mm` / `53.0 mm` idle
  returned `19.60 x 18.55 mm` / `62.0 mm` (measured 2026-09-06). What *is* invariant is the
  set of properties the tests check — every footprint placed, no overlapping courtyards, the
  file reparsing — plus the byte count for a given placement. The 20-second figure is the
  budget, not a benchmark.

### Continuous integration

[`.github/workflows/ci.yml`](.github/workflows/ci.yml) runs `ruff check` over seven
directories (`engine service scripts desktop googleapps zoombot teamsbot`) and `pytest -q`
over all eight `testpaths` on **Ubuntu, macOS, and Windows** against Python 3.11, on every
push to `main` and every pull request, installing `".[dev,agents,cloud,adk,cad]"` so the
enclosure-kernel tests actually run rather than skipping green. `fail-fast` is off, so one
platform failing does not mask the others. **Four** further jobs run: `web` (the SPA bundle
and its Vitest suite), `app` and `desktop` (the two Tauri shells), and `docker`, which
builds the container image and is the only thing that exercises the `Dockerfile`. No job
deploys anything.

---

## Contributing

`CONTRIBUTING.md` has the setup, the checks to run before opening a PR, and the
conventions that are easy to violate by accident — the integer-nanometre rule, the
Y-up/Y-down coordinate boundary, and which top-level directories are dead code.

## License

MIT — see [LICENSE](LICENSE).

Dependencies: `kiutils` (MIT), OR-Tools (Apache-2.0).

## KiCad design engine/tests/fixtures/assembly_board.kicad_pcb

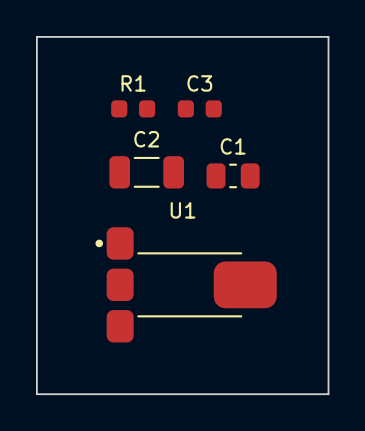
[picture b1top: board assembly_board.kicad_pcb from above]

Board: 2 copper layers, 16.2 x 19.9 mm, 5 parts (0 on the bottom side), 4 nets, no tracks yet.

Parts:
C1: 10uF; C_0805
C2: 22uF; C_1206
C3: 100nF; C_0603
R1: 1k; R_0603
U1: AMS1117-3.3; SOT-223-3_TabPin2

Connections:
+3V3: C2.1, R1.1, U1.2
GND: C1.2, C2.2, C3.2, U1.1
OUT: C3.1, R1.2
VIN: C1.1, U1.3

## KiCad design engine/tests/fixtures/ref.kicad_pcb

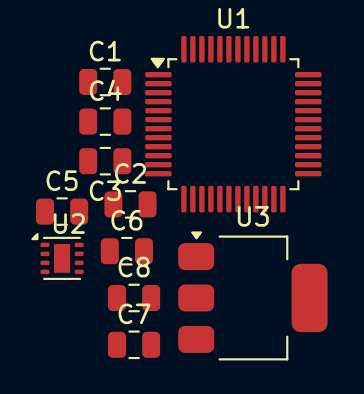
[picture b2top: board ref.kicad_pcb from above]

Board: 2 copper layers, 11 parts (0 on the bottom side), 6 nets, no tracks yet.

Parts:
C1, C2, C5, C6: 0.1ÂµF; C_0805_2012Metric
C3, C4: 10 pF; C_0805_2012Metric
C7, C8: 22ÂµF; C_0805_2012Metric
U1: STM32F030C8Tx; LQFP-48_7x7mm_P0.5mm
U2: DRV8838; WSON-8-1EP_2x2mm_P0.5mm_EP0.9x1.6mm
U3: AMS1117; SOT-223-3_TabPin2

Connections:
0_device_pin_1: C1.1, C1.2, C6.1, C6.2, U1.1, U2.8
0_device_pin_6: C3.1, C3.2, C4.1, C4.2, U1.5, U1.6
0_device_pin_13: C2.1, C2.2, U1.13
0_device_pin_31: U1.12, U1.31, U2.4, U3.1
2_device_pin_2: C8.1, C8.2, U3.2
2_device_pin_3: C5.1, C5.2, C7.1, C7.2, U2.1, U3.3
